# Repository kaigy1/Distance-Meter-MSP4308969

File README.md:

## Distance Finder- MSP4308969

distance finder using a ultrasonic sensor  
and the MSP4308969 chip from texas instrument

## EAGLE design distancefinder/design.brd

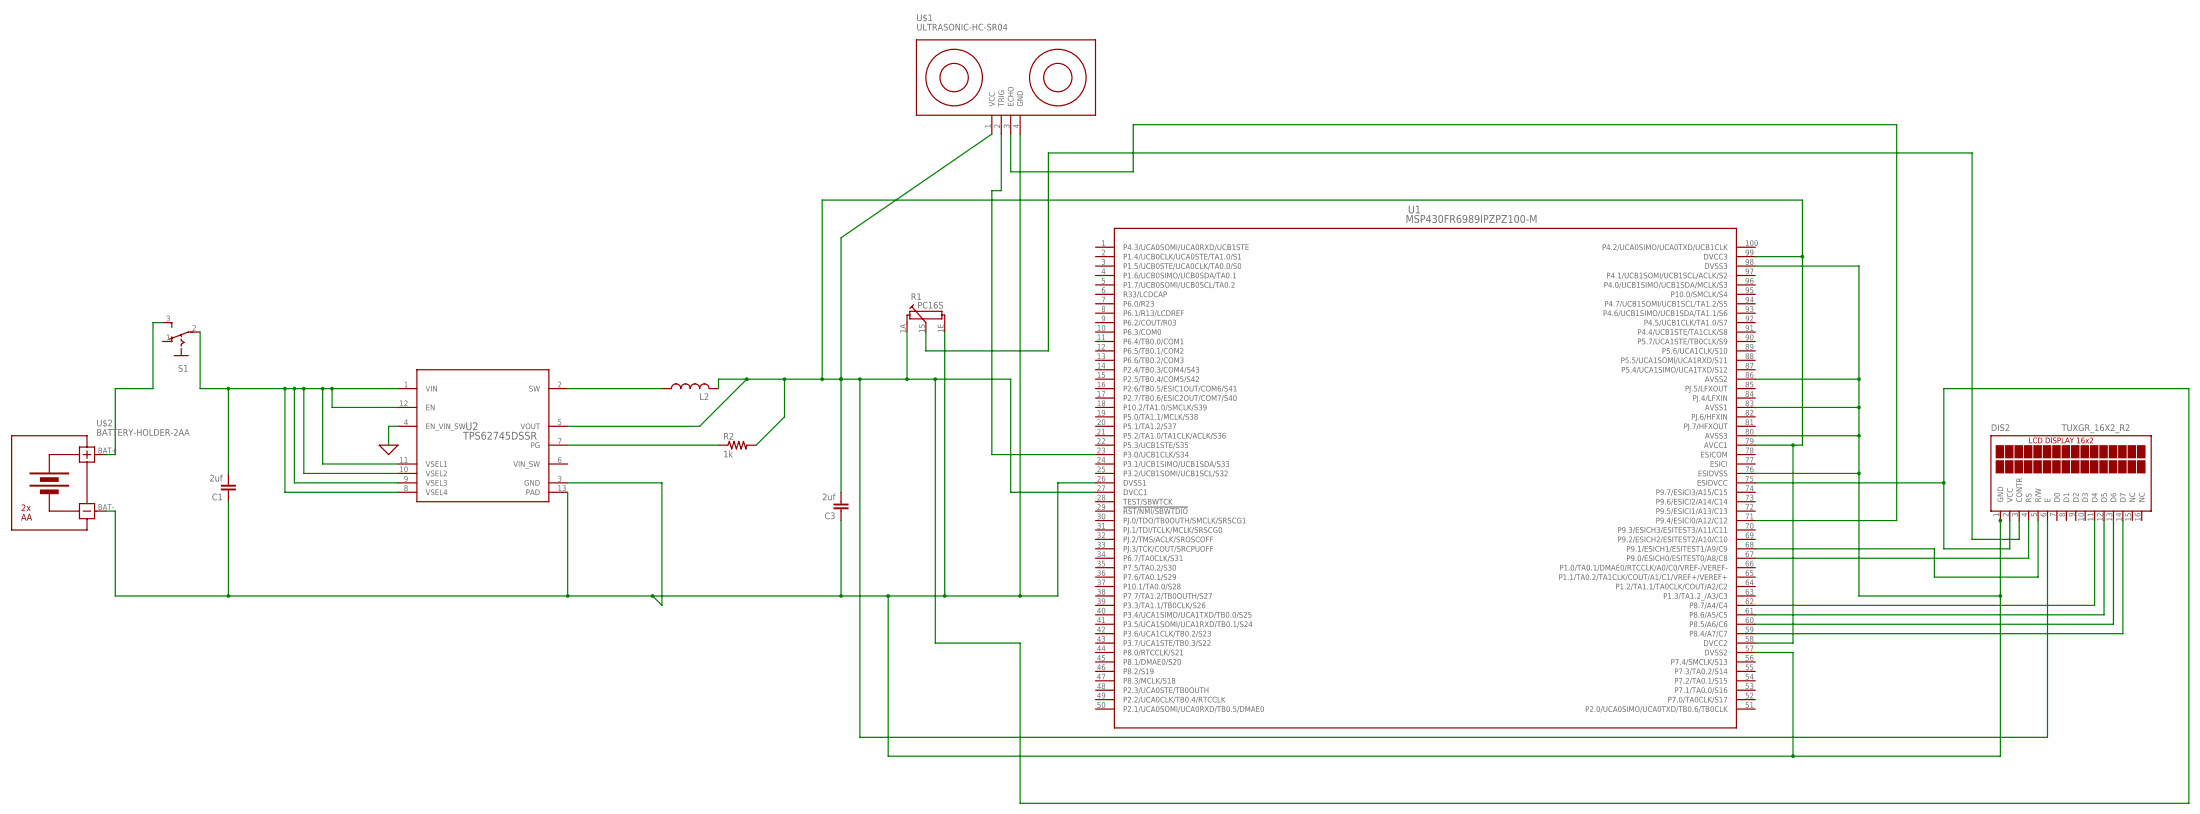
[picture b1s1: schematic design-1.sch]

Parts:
C1, C3: 2uf; C0603
DIS2: TUXGR_16X2_R2
L2: L-US0204/5; 0204/5
R1: PC16S
R2: 1k; R0603
S1: 255SB
U1: MSP430FR6989IPZPZ100-M; PZ100-M
U2: TPS62745DSSR; DSS0012A
U$1: ULTRASONIC-HC-SR04
U$2: BATTERY-HOLDER-2AA

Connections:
0: U2.4 (EN_VIN_SW)
unnamed: C1.2, S1.2, U2.1 (VIN), U2.8 (VSEL4), U2.9 (VSEL3), U2.10 (VSEL2), U2.11 (VSEL1), U2.12 (EN)
unnamed: C3.2, DIS2.2 (VCC), DIS2.6 (E), L2.2, R1.1A, R2.2, U1.27 (DVCC1), U1.58 (DVCC2), U1.75 (ESIDVCC), U1.79 (AVCC1), U1.99 (DVCC3), U2.5 (VOUT), U$1.1 (VCC)
unnamed: R2.1, U2.7 (PG)
unnamed: S1.3 (S), U$2.BAT+
unnamed: DIS2.14 (D7), U1.59 (P8.4/A7/C7)
unnamed: L2.1, U2.2 (SW)
unnamed: U1.71 (P9.4/ESICI0/A12/C12), U$1.3 (ECHO)
unnamed: U1.23 (P3.0/UCB1CLK/S34), U$1.2 (TRIG)
unnamed: DIS2.13 (D6), U1.60 (P8.5/A6/C6)
unnamed: DIS2.12 (D5), U1.61 (P8.6/A5/C5)
unnamed: DIS2.11 (D4), U1.62 (P8.7/A4/C4)
unnamed: C1.1, C3.1, DIS2.1 (GND), R1.1E, U1.26 (DVSS1), U1.57 (DVSS2), U1.76 (ESIDVSS), U1.80 (AVSS3), U1.83 (AVSS1), U1.86 (AVSS2), U1.98 (DVSS3), U2.3 (GND), U2.13 (PAD), U$1.4 (GND), U$2.BAT-
unnamed: DIS2.4 (RS), U1.67 (P9.0/ESICH0/ESITEST0/A8/C8)
unnamed: DIS2.5 (R/W), U1.68 (P9.1/ESICH1/ESITEST1/A9/C9)
unnamed: DIS2.3 (CONTR), R1.1S
VIN_SW: U2.6 (VIN_SW)

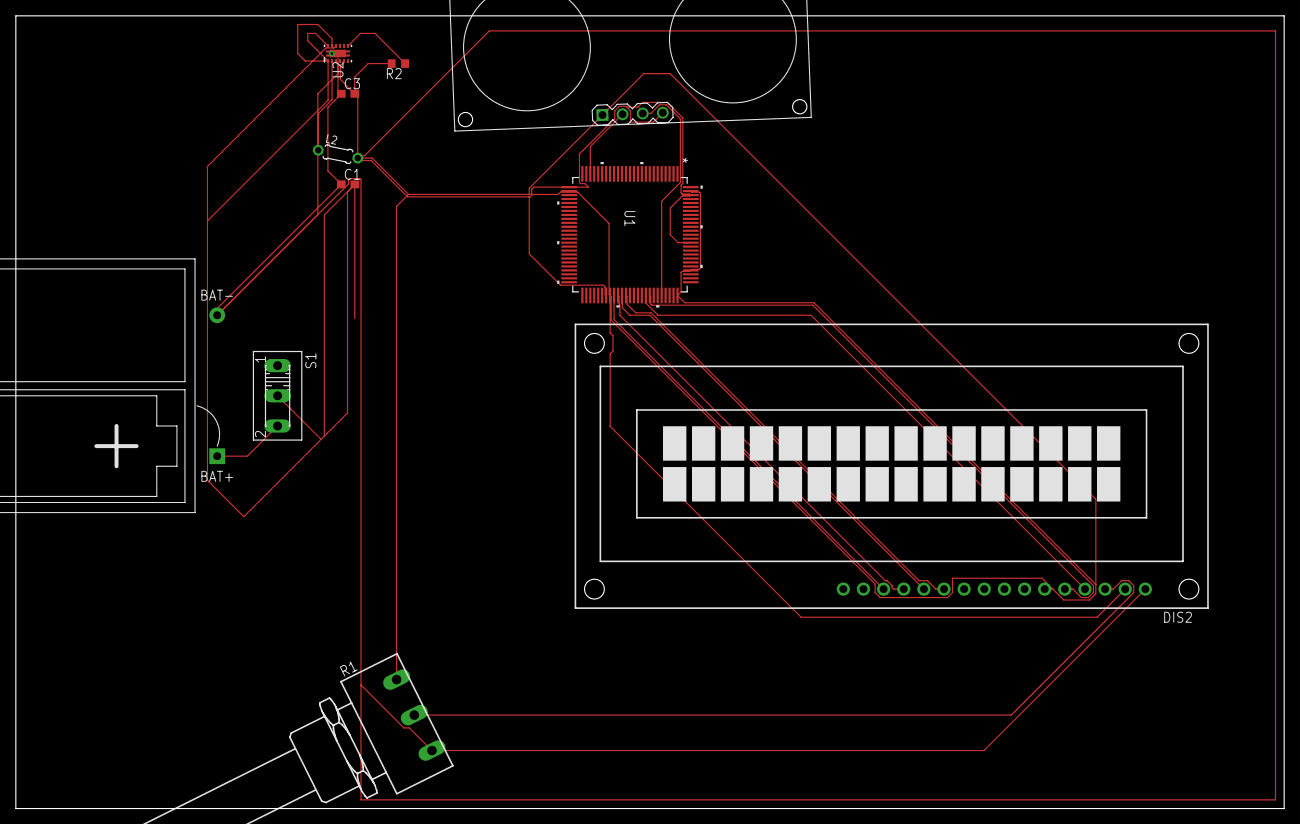
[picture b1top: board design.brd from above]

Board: 2 copper layers, 160.0 x 100.0 mm, 11 parts (0 on the bottom side), 15 nets.

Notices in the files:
parts and their libraries:
diy-modules: Released under the Creative Commons Attribution 4.0 International License: http://creativecommons.org/licenses/by/4.0
